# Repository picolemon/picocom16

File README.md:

# Picocom16
A DIY breadboard computer based on four RP2350 micro controllers that can be built without any soldering.

## Features
Easy build with no soldering.

Fast debugging using VSCode and a usb cable.

Double buffered frame buffer with simple gpu for drawing.

Async DMA bus distributes graphics and sound to each core.

Written in C with a clear and simple api.

## Display

Frame buffer: 320×224, 16 bit color palette, 60 Hz.    

GPU Method: Command dispatch and Tiling.

Blend modes:  4bit alpha composite, Additive blending.

## Memory

System RAM: 512 KB SRAM

VRAM: 512 KB SRAM

FB: 512 KB SRAM

Audio RAM: 512 KB SRAM

## DMA
VDP1 Bus - System to VDP gpu command stream async.

VDP2 Bus - VDP1 to VDP2 tile stream.

APU Bus - System to APU audio commands, audio streams, HID inputs and SD Card IO.

## Storage
Physics format: Format: SD memory card.

File System: Fat32.

## Audio
DSP mixer: play, pause, pan & frequency.

Audio formats: Raw PCM 16, OGG vorbis.

Streaming: Audio stream buffer for seamless audio looping and streaming from System core.

Rate: 11 Khz.

Output: Stereo output via 3mm jack.

Channels: 32 channels ( sfx or ogg in any combination ).

## Cores
APU - Dedicated audio processor. [ [src](sw/apu) ] [ [uf2](firmware/apu.uf2) ]

System - Game processor for game logic, building graphics and audio commands.  [ [demos](sw/demos) ] 

VDP1 - Graphics tile generator.  [ [src](sw/vdp1) ] [ [uf2](firmware/vdp1.uf2) ]

VDP2 - Tile compositor and DVI output.  [ [src](sw/vdp2) ] [ [uf2](firmware/vdp2.uf2) ]

## Examples

gfx_demo [ [src](sw/demos/gfx_demo) ] [ [uf2](firmware/gfx_demo.uf2) ]

input_demo  [ [src](sw/demos/gfx_demo) ] [ [uf2](firmware/gfx_demo.uf2) ]

minerload   [ [demo](https://picocom16.itch.io/minerload) ] [ [uf2](firmware/minerload.uf2) ]

## Components BOM

All components can be source from amazon or other suppliers.

    1 x Breadboard kit - SUNFOUNDER 5PCS Breadboards Kit Include 3PCS 830 Point 2PCS 400 Point Solderless Breadboard Compatible with Arduino Proto Shield Distribution Connecting Blocks 

    1 x Wire kit - 560 Pcs Jumper Wire Kit, 14 Lengths Assorted Preformed Breadboard Jumper Wires, Male to Male Solderless Jumper Cables with Storage Box for Prototyping, LED Strips, and Test Circuits 

    4 x Pre-Soldered Raspberry Pi Pico 2 with Header RP2350 Microcontroller Board Mini Board Kit Based on RP2350 Chip,Dual-core & Dual-architecture,Support C/C++/Python 

    1 x PCM5102 DAC Decoder Module I2S Interface GY-PCM5102 PHAT Format Player Board Digital-to-Analog Converter Voice Module for Arduino, Raspberry Pi with 3.5mm Jack Audio Cable, Dupont Cable 

    1 x AZDelivery Micro SD SPI Storage Board TF Memory Card Adapter Shield Module 5V compatible with Arduino Including E-Book! (Pack of 3) 

    1 x Adafruit DVI Breakout Board - For HDMI Source Devices 

    1 x 18pcs USB to DIP Breakout Adapter Converter Mini 5p USB/2.54 mm 4p/USB 2.0 4p/USB 3.0 Flat/Micro USB Type B/USB Type-B Square PCB Power Breakout Board Module

## Build guide
This is what the fully assembled breadboard looks like:

See [docs/guides/picocom16-breadboard/Build-guide.md](docs/guides/picocom16-breadboard/Build-guide.md)

## System dependencies

VSCode: https://code.visualstudio.com/

Pico sdk: https://marketplace.visualstudio.com/items?itemName=raspberry-pi.raspberry-pi-pico

Asset tooling python deps
```
pip install bdfparser
```

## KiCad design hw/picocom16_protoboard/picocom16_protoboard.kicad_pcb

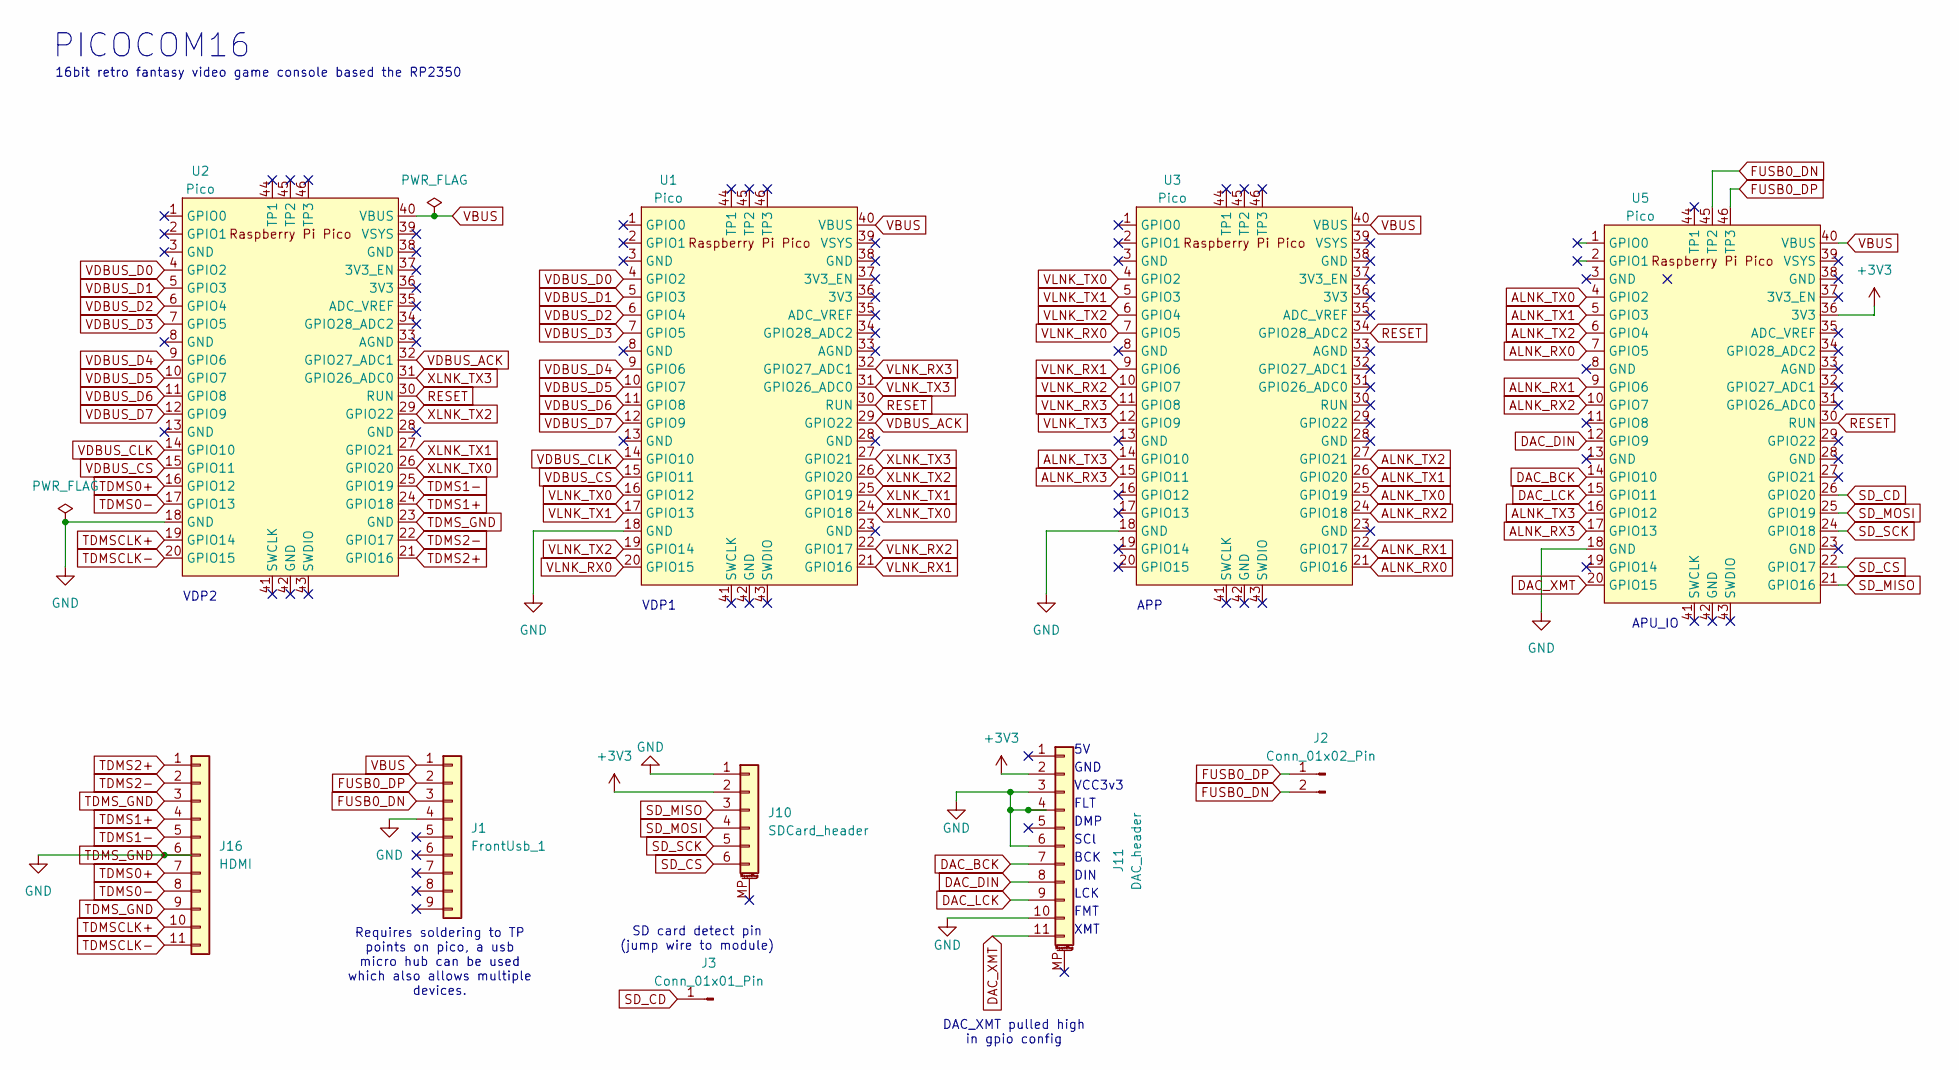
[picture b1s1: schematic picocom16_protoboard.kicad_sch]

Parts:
J1: FrontUsb_1; PinHeader_1x09_P2.54mm_Vertical
J2: Conn_01x02_Pin; PinHeader_1x02_P2.54mm_Vertical
J3: Conn_01x01_Pin; PinHeader_1x01_P2.54mm_Vertical
J10: SDCard_header; PinHeader_1x06_P2.54mm_Vertical
J11: DAC_header; PinHeader_1x11_P2.54mm_Vertical
J16: HDMI; PinHeader_1x11_P2.54mm_Vertical
U1, U2, U3, U5: Pico; RPi_Pico_SMD_TH

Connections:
+3V3: J10.2, J11.2, U5.36 (3V3)
ALNK_RX0: U3.21 (GPIO16), U5.7 (GPIO5)
ALNK_RX1: U3.22 (GPIO17), U5.9 (GPIO6)
ALNK_RX2: U3.24 (GPIO18), U5.10 (GPIO7)
ALNK_RX3: U3.15 (GPIO11), U5.17 (GPIO13)
ALNK_TX0: U3.25 (GPIO19), U5.4 (GPIO2)
ALNK_TX1: U3.26 (GPIO20), U5.5 (GPIO3)
ALNK_TX2: U3.27 (GPIO21), U5.6 (GPIO4)
ALNK_TX3: U3.14 (GPIO10), U5.16 (GPIO12)
DAC_BCK: J11.7, U5.14 (GPIO10)
DAC_DIN: J11.8, U5.12 (GPIO9)
DAC_LCK: J11.9, U5.15 (GPIO11)
DAC_XMT: J11.11, U5.20 (GPIO15)
FUSB0_DN: J1.3, J2.2, U5.45 (TP2)
FUSB0_DP: J1.2, J2.1, U5.46 (TP3)
RESET: U1.30 (RUN), U2.30 (RUN), U3.34 (GPIO28_ADC2), U5.30 (RUN)
SD_CD: J3.1, U5.26 (GPIO20)
SD_CS: J10.6, U5.22 (GPIO17)
SD_MISO: J10.3, U5.21 (GPIO16)
SD_MOSI: J10.4, U5.25 (GPIO19)
SD_SCK: J10.5, U5.24 (GPIO18)
TDMS0+: J16.7, U2.16 (GPIO12)
TDMS0-: J16.8, U2.17 (GPIO13)
TDMS1+: J16.4, U2.24 (GPIO18)
TDMS1-: J16.5, U2.25 (GPIO19)
TDMS2+: J16.1, U2.21 (GPIO16)
TDMS2-: J16.2, U2.22 (GPIO17)
TDMSCLK+: J16.10, U2.19 (GPIO14)
TDMSCLK-: J16.11, U2.20 (GPIO15)
TDMS_GND: J1.4, J10.1, J11.3, J11.4, J11.6, J11.10, J16.3, J16.6, J16.9, U1.18 (GND), U2.18 (GND), U2.23 (GND), U3.18 (GND), U5.18 (GND)
VBUS: J1.1, U1.40 (VBUS), U2.40 (VBUS), U3.40 (VBUS), U5.40 (VBUS)
VDBUS_ACK: U1.29 (GPIO22), U2.32 (GPIO27_ADC1)
VDBUS_CLK: U1.14 (GPIO10), U2.14 (GPIO10)
VDBUS_CS: U1.15 (GPIO11), U2.15 (GPIO11)
VDBUS_D0: U1.4 (GPIO2), U2.4 (GPIO2)
VDBUS_D1: U1.5 (GPIO3), U2.5 (GPIO3)
VDBUS_D2: U1.6 (GPIO4), U2.6 (GPIO4)
VDBUS_D3: U1.7 (GPIO5), U2.7 (GPIO5)
VDBUS_D4: U1.9 (GPIO6), U2.9 (GPIO6)
VDBUS_D5: U1.10 (GPIO7), U2.10 (GPIO7)
VDBUS_D6: U1.11 (GPIO8), U2.11 (GPIO8)
VDBUS_D7: U1.12 (GPIO9), U2.12 (GPIO9)
VLNK_RX0: U1.20 (GPIO15), U3.7 (GPIO5)
VLNK_RX1: U1.21 (GPIO16), U3.9 (GPIO6)
VLNK_RX2: U1.22 (GPIO17), U3.10 (GPIO7)
VLNK_RX3: U1.32 (GPIO27_ADC1), U3.11 (GPIO8)
VLNK_TX0: U1.16 (GPIO12), U3.4 (GPIO2)
VLNK_TX1: U1.17 (GPIO13), U3.5 (GPIO3)
VLNK_TX2: U1.19 (GPIO14), U3.6 (GPIO4)
VLNK_TX3: U1.31 (GPIO26_ADC0), U3.12 (GPIO9)
XLNK_TX0: U1.24 (GPIO18), U2.26 (GPIO20)
XLNK_TX1: U1.25 (GPIO19), U2.27 (GPIO21)
XLNK_TX2: U1.26 (GPIO20), U2.29 (GPIO22)
XLNK_TX3: U1.27 (GPIO21), U2.31 (GPIO26_ADC0)

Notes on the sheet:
APP
VDP1
VCC3v3
FMT
DMP
DIN
SD card detect pin (jump wire to module)
16bit retro fantasy video game console based the RP2350
XMT
VDP2
FLT
GND
SCl
DAC_XMT pulled high in gpio config
Requires soldering to TP points on pico, a usb micro hub can be used which also allows multiple devices.
PICOCOM16
APU_IO
LCK
BCK

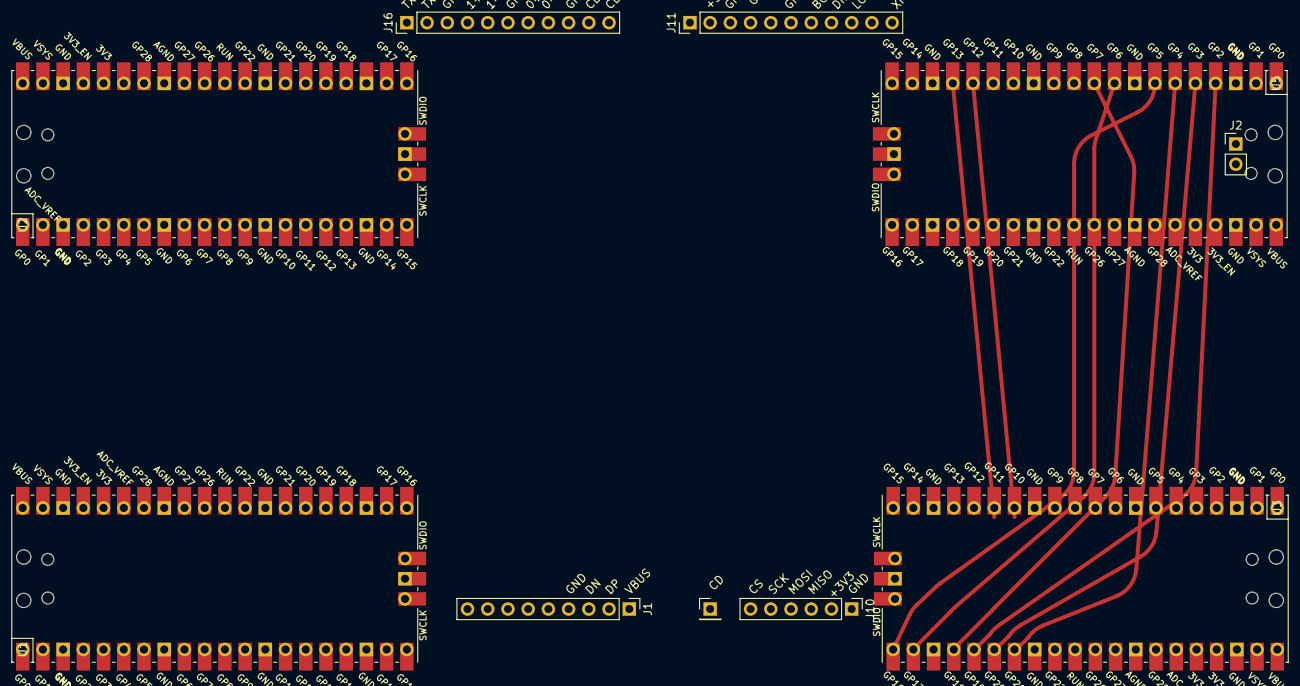
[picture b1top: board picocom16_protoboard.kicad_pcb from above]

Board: 18 copper layers, 10 parts (0 on the bottom side), 54 nets.

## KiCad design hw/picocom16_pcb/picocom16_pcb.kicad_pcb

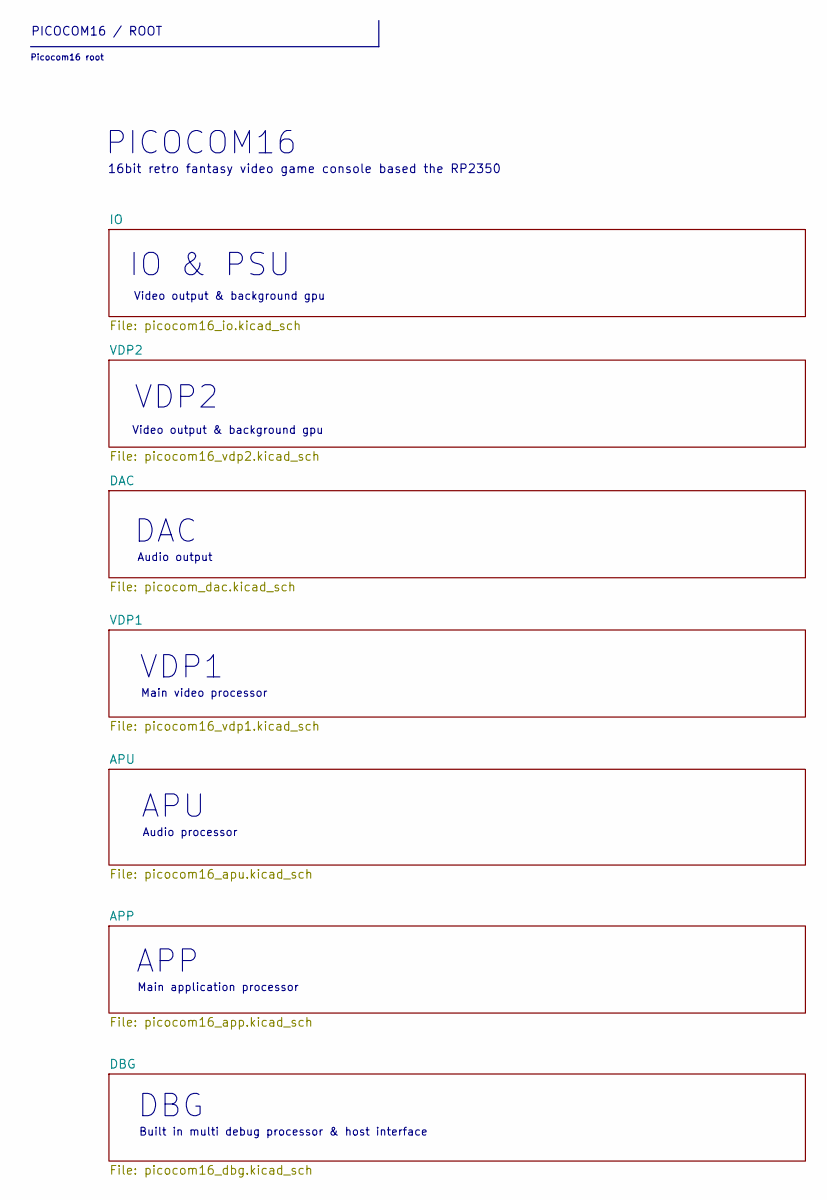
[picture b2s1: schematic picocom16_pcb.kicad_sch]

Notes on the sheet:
VDP2
Main application processor
Audio output
Built in multi debug processor & host interface
PICOCOM16 / ROOT
Video output & background gpu
VDP1
IO & PSU
16bit retro fantasy video game console based the RP2350
APP
Picocom16 root
Main video processor
DBG
APU
PICOCOM16
DAC
Audio processor

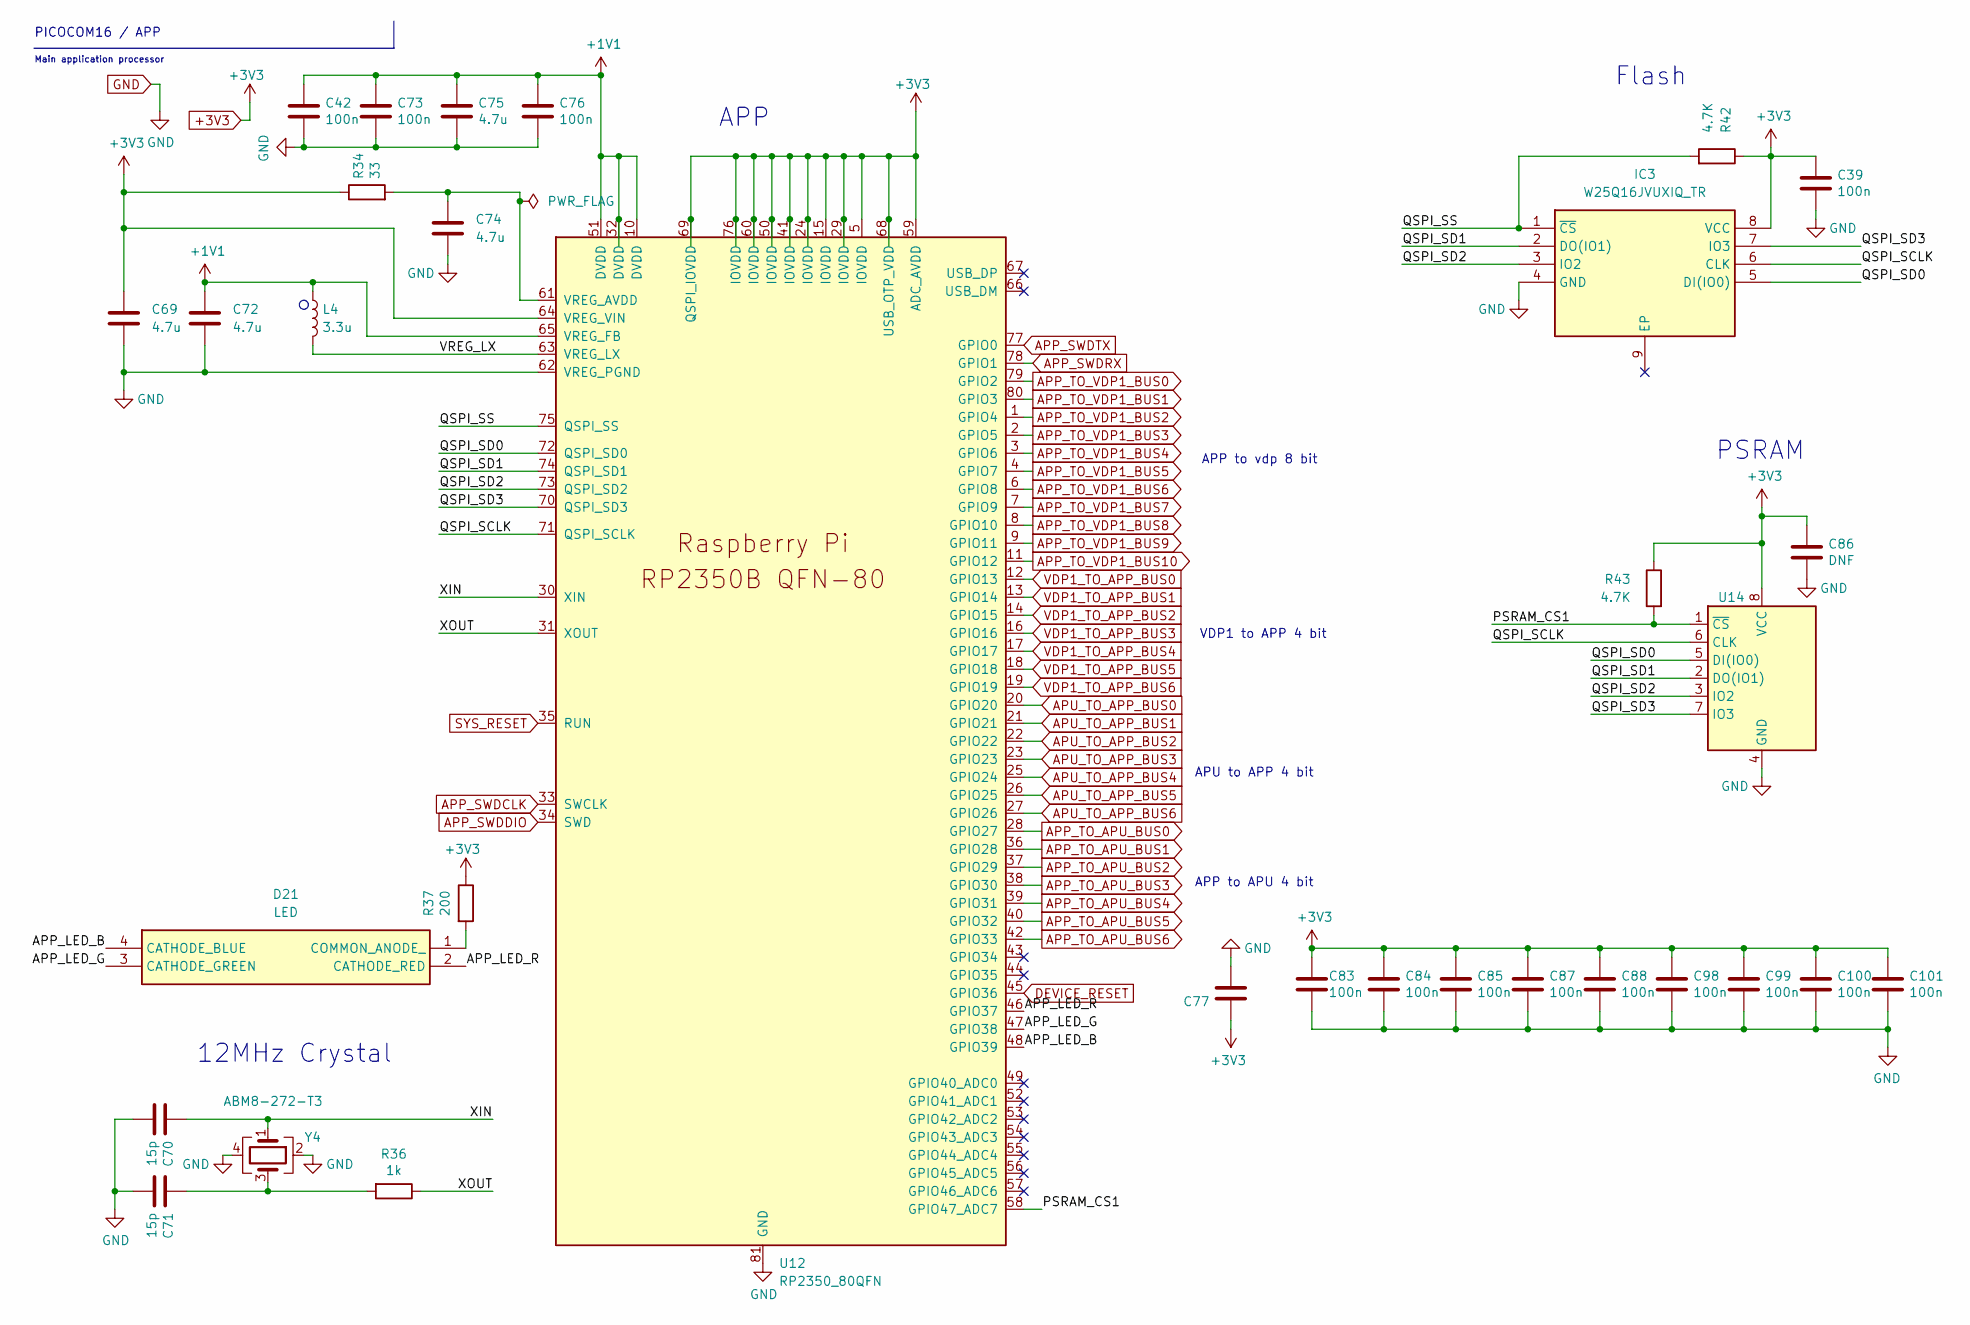
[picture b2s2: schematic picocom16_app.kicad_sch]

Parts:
C39, C42, C73, C76, C83, C84, C85, C87, C88, C98, C99, C100, C101: 100n; C_0402_1005Metric
C69, C72, C74, C75: 4.7u; C_0402_1005Metric
C70, C71: 15p; C_0402_1005Metric
C77: 10u; C_0805_2012Metric
C86: DNF; C_0402_1005Metric
D21: LRTBR48G-P9Q7-1+R7S5-26+NP-68; LRTBR48GP9Q71R7S526NP68; Mouser Part Number 720-LRTBR48GP9A3521
IC3: W25Q16JVUXIQ_TR; SON50P300X200X60-9N; Mouser Part Number 454-W25Q16JVUXIQTR
L4: 3.3u; L_0805_2012Metric
R34: 33; R_0402_1005Metric
R36: 1k; R_0402_1005Metric
R37: 200; R_0402_1005Metric
R42, R43: 4.7K; R_0402_1005Metric
U12: RP2350_80QFN; RP2350-QFN-80-1EP_10x10_P0.4mm_EP3.4x3.4mm_ThermalVias
U14: SOIC-8_5.23x5.23mm_P1.27mm
Y4: ABM8-272-T3; ABM8272T3

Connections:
+1V1: C42.1, C72.1, C73.1, C75.1, C76.1, L4.1, U12.10 (DVDD), U12.32 (DVDD), U12.51 (DVDD), U12.65 (VREG_FB); also elsewhere on the board
+3V3: C39.1, C69.1, C77.1, C83.1, C84.1, C85.1, C86.1, C87.1, C88.1, C98.1, C99.1, C100.1, C101.1, IC3.8 (VCC), R34.1, R37.1, R42.1, R43.1, U12.5 (IOVDD), U12.15 (IOVDD), U12.24 (IOVDD), U12.29 (IOVDD), U12.41 (IOVDD), U12.50 (IOVDD), U12.59 (ADC_AVDD), U12.60 (IOVDD), U12.64 (VREG_VIN), U12.68 (USB_OTP_VDD), U12.69 (QSPI_IOVDD), U12.76 (IOVDD), U14.8 (VCC); also elsewhere on the board
/APP/APP_LED_B: D21.4 (CATHODE_BLUE), U12.48 (GPIO39)
/APP/APP_LED_G: D21.3 (CATHODE_GREEN), U12.47 (GPIO38)
/APP/APP_LED_R: D21.2 (CATHODE_RED), U12.46 (GPIO37)
/APP/PSRAM_CS1: R43.2, U12.58 (GPIO47_ADC7), U14.1 (~CS)
/APP/QSPI_SCLK: IC3.6 (CLK), U12.71 (QSPI_SCLK), U14.6 (CLK)
/APP/QSPI_SD0: IC3.5 (DI(IO0)), U12.72 (QSPI_SD0), U14.5 (DI(IO0))
/APP/QSPI_SD1: IC3.2 (DO(IO1)), U12.74 (QSPI_SD1), U14.2 (DO(IO1))
/APP/QSPI_SD2: IC3.3 (IO2), U12.73 (QSPI_SD2), U14.3 (IO2)
/APP/QSPI_SD3: IC3.7 (IO3), U12.70 (QSPI_SD3), U14.7 (IO3)
/APP/QSPI_SS: IC3.1 (~CS), R42.2, U12.75 (QSPI_SS)
/APP/VREG_LX: L4.2, U12.63 (VREG_LX)
/APP/XIN: C70.1, U12.30 (XIN), Y4.1
/APP/XOUT: R36.1, U12.31 (XOUT)
APP_SWDCLK: U12.33 (SWCLK); also elsewhere on the board
APP_SWDDIO: U12.34 (SWD); also elsewhere on the board
APP_SWDRX: U12.78 (GPIO1); also elsewhere on the board
APP_SWDTX: U12.77 (GPIO0); also elsewhere on the board
APP_TO_APU_BUS0: U12.28 (GPIO27); also elsewhere on the board
APP_TO_APU_BUS1: U12.36 (GPIO28); also elsewhere on the board
APP_TO_APU_BUS2: U12.37 (GPIO29); also elsewhere on the board
APP_TO_APU_BUS3: U12.38 (GPIO30); also elsewhere on the board
APP_TO_APU_BUS4: U12.39 (GPIO31); also elsewhere on the board
APP_TO_APU_BUS5: U12.40 (GPIO32); also elsewhere on the board
APP_TO_APU_BUS6: U12.42 (GPIO33); also elsewhere on the board
APP_TO_VDP1_BUS0: U12.79 (GPIO2); also elsewhere on the board
APP_TO_VDP1_BUS1: U12.80 (GPIO3); also elsewhere on the board
APP_TO_VDP1_BUS2: U12.1 (GPIO4); also elsewhere on the board
APP_TO_VDP1_BUS3: U12.2 (GPIO5); also elsewhere on the board
APP_TO_VDP1_BUS4: U12.3 (GPIO6); also elsewhere on the board
APP_TO_VDP1_BUS5: U12.4 (GPIO7); also elsewhere on the board
APP_TO_VDP1_BUS6: U12.6 (GPIO8); also elsewhere on the board
APP_TO_VDP1_BUS7: U12.7 (GPIO9); also elsewhere on the board
APP_TO_VDP1_BUS8: U12.8 (GPIO10); also elsewhere on the board
APP_TO_VDP1_BUS9: U12.9 (GPIO11); also elsewhere on the board
APP_TO_VDP1_BUS10: U12.11 (GPIO12); also elsewhere on the board
APU_TO_APP_BUS0: U12.20 (GPIO20); also elsewhere on the board
APU_TO_APP_BUS1: U12.21 (GPIO21); also elsewhere on the board
APU_TO_APP_BUS2: U12.22 (GPIO22); also elsewhere on the board
APU_TO_APP_BUS3: U12.23 (GPIO23); also elsewhere on the board
APU_TO_APP_BUS4: U12.25 (GPIO24); also elsewhere on the board
APU_TO_APP_BUS5: U12.26 (GPIO25); also elsewhere on the board
APU_TO_APP_BUS6: U12.27 (GPIO26); also elsewhere on the board
DEVICE_RESET: U12.45 (GPIO36); also elsewhere on the board
GND: C39.2, C42.2, C69.2, C70.2, C71.2, C72.2, C73.2, C74.2, C75.2, C76.2, C77.2, C83.2, C84.2, C85.2, C86.2, C87.2, C88.2, C98.2, C99.2, C100.2, C101.2, IC3.4 (GND), U12.62 (VREG_PGND), U12.81 (GND), U14.4 (GND), Y4.2, Y4.4; also elsewhere on the board
unnamed: C71.1, R36.2, Y4.3
unnamed: D21.1 (COMMON_ANODE_), R37.2
unnamed: C74.1, R34.2, U12.61 (VREG_AVDD)
SYS_RESET: U12.35 (RUN); also elsewhere on the board
VDP1_TO_APP_BUS0: U12.12 (GPIO13); also elsewhere on the board
VDP1_TO_APP_BUS1: U12.13 (GPIO14); also elsewhere on the board
VDP1_TO_APP_BUS2: U12.14 (GPIO15); also elsewhere on the board
VDP1_TO_APP_BUS3: U12.16 (GPIO16); also elsewhere on the board
VDP1_TO_APP_BUS4: U12.17 (GPIO17); also elsewhere on the board
VDP1_TO_APP_BUS5: U12.18 (GPIO18); also elsewhere on the board
VDP1_TO_APP_BUS6: U12.19 (GPIO19); also elsewhere on the board

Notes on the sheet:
PSRAM
APP to APU 4 bit
APP to vdp 8 bit
APP
APU to APP 4 bit
12MHz Crystal
PICOCOM16 / APP
Main application processor
VDP1 to APP 4 bit
Flash

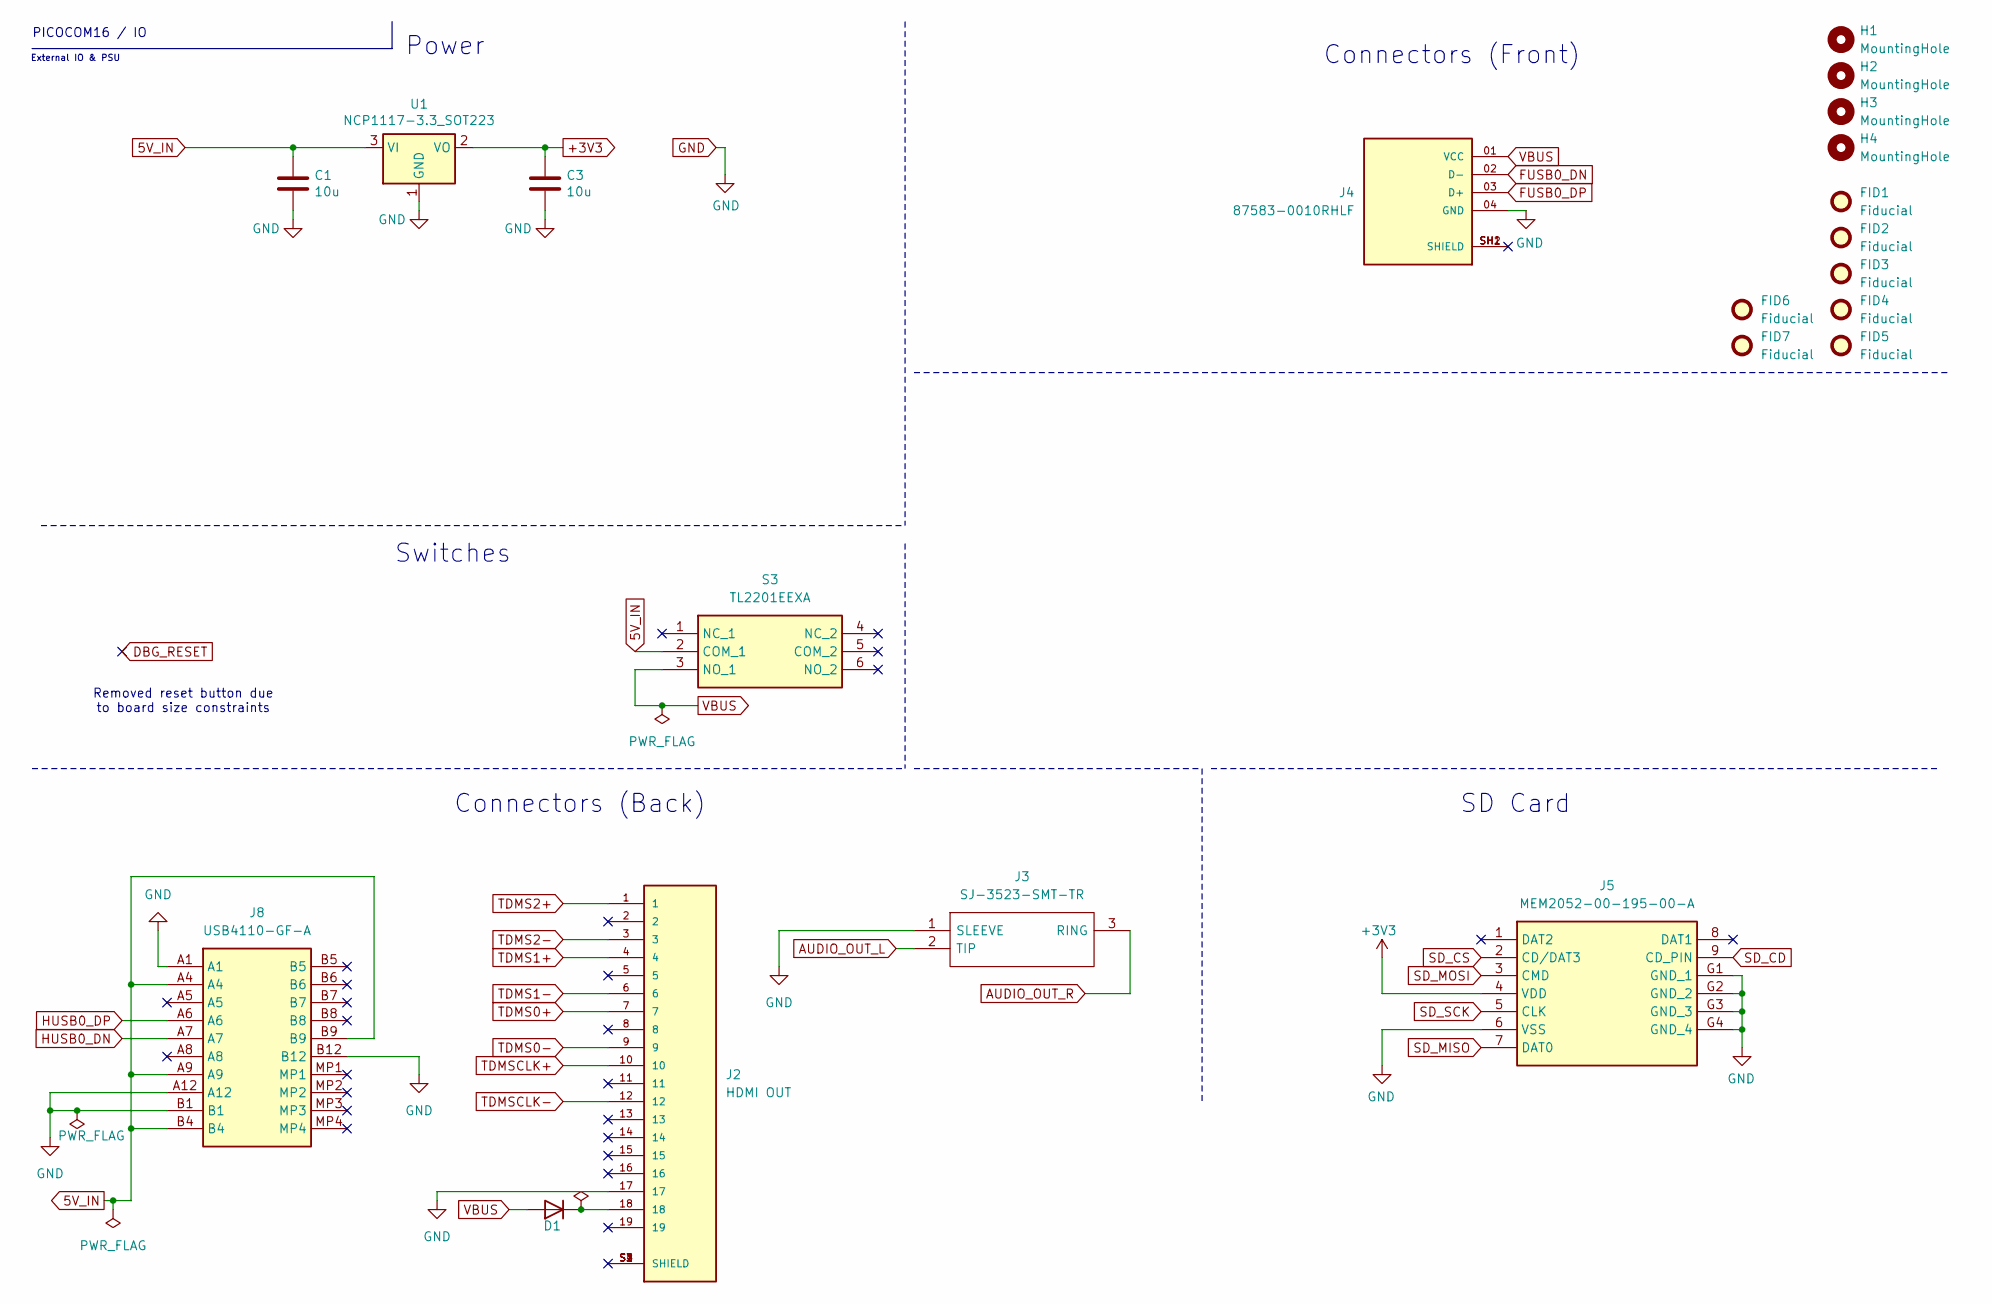
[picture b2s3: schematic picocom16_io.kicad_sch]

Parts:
C1, C3: 10u; C_0805_2012Metric
D1: D; SODFL1608X70N
FID1, FID2, FID3, FID4, FID6, FID7: Fiducial; Fiducial_1mm_Mask2mm
FID5: Fiducial; Fiducial_0.5mm_Mask1.5mm
H1, H2, H3, H4: MountingHole; MountingHole_2.7mm_M2.5
J2: HDMI OUT; STEWART_SS-53000-001; PARTREV A0
J3: SJ-3523-SMT-TR; SJ3523SMTTR; Mouser Part Number 490-SJ-3523-SMT-TR
J4: 87583-0010RHLF; AMPHENOL_87583-0010RHLF; PARTREV AD
J5: MEM2052-00-195-00-A; MEM20520019500A; Mouser Part Number 640-MEM20520019500A
J8: USB4110-GF-A; USB4110GFA; Mouser Part Number 640-USB4110-GF-A
S3: TL2201EEXA; Mouser Part Number 612-TL2201EEXA
U1: NCP1117-3.3_SOT223; SOT-223-3_TabPin2

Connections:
5V_IN: C1.1, J8.A4, J8.A9, J8.B4, J8.B9, S3.2 (COM_1), U1.3 (VI)
+3V3: C3.1, J5.4 (VDD), U1.2 (VO); also elsewhere on the board
AUDIO_OUT_L: J3.2 (TIP); also elsewhere on the board
AUDIO_OUT_R: J3.3 (RING); also elsewhere on the board
FUSB0_DN: J4.02 (D-); also elsewhere on the board
FUSB0_DP: J4.03 (D+); also elsewhere on the board
GND: C1.2, C3.2, J2.17, J3.1 (SLEEVE), J4.04 (GND), J5.6 (VSS), J5.G1 (GND_1), J5.G2 (GND_2), J5.G3 (GND_3), J5.G4 (GND_4), J8.A1, J8.A12, J8.B1, J8.B12, U1.1 (GND); also elsewhere on the board
HUSB0_DN: J8.A7; also elsewhere on the board
HUSB0_DP: J8.A6; also elsewhere on the board
unnamed: D1.1 (K), J2.18
SD_CD: J5.9 (CD_PIN); also elsewhere on the board
SD_CS: J5.2 (CD/DAT3); also elsewhere on the board
SD_MISO: J5.7 (DAT0); also elsewhere on the board
SD_MOSI: J5.3 (CMD); also elsewhere on the board
SD_SCK: J5.5 (CLK); also elsewhere on the board
TDMS0+: J2.7; also elsewhere on the board
TDMS0-: J2.9; also elsewhere on the board
TDMS1+: J2.4; also elsewhere on the board
TDMS1-: J2.6; also elsewhere on the board
TDMS2+: J2.1; also elsewhere on the board
TDMS2-: J2.3; also elsewhere on the board
TDMSCLK+: J2.10; also elsewhere on the board
TDMSCLK-: J2.12; also elsewhere on the board
VBUS: D1.2 (A), J4.01 (VCC), S3.3 (NO_1)

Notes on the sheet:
External IO & PSU
PICOCOM16 / IO
Power
Connectors (Front)
Switches
Removed reset button due to board size constraints
Connectors (Back)
SD Card

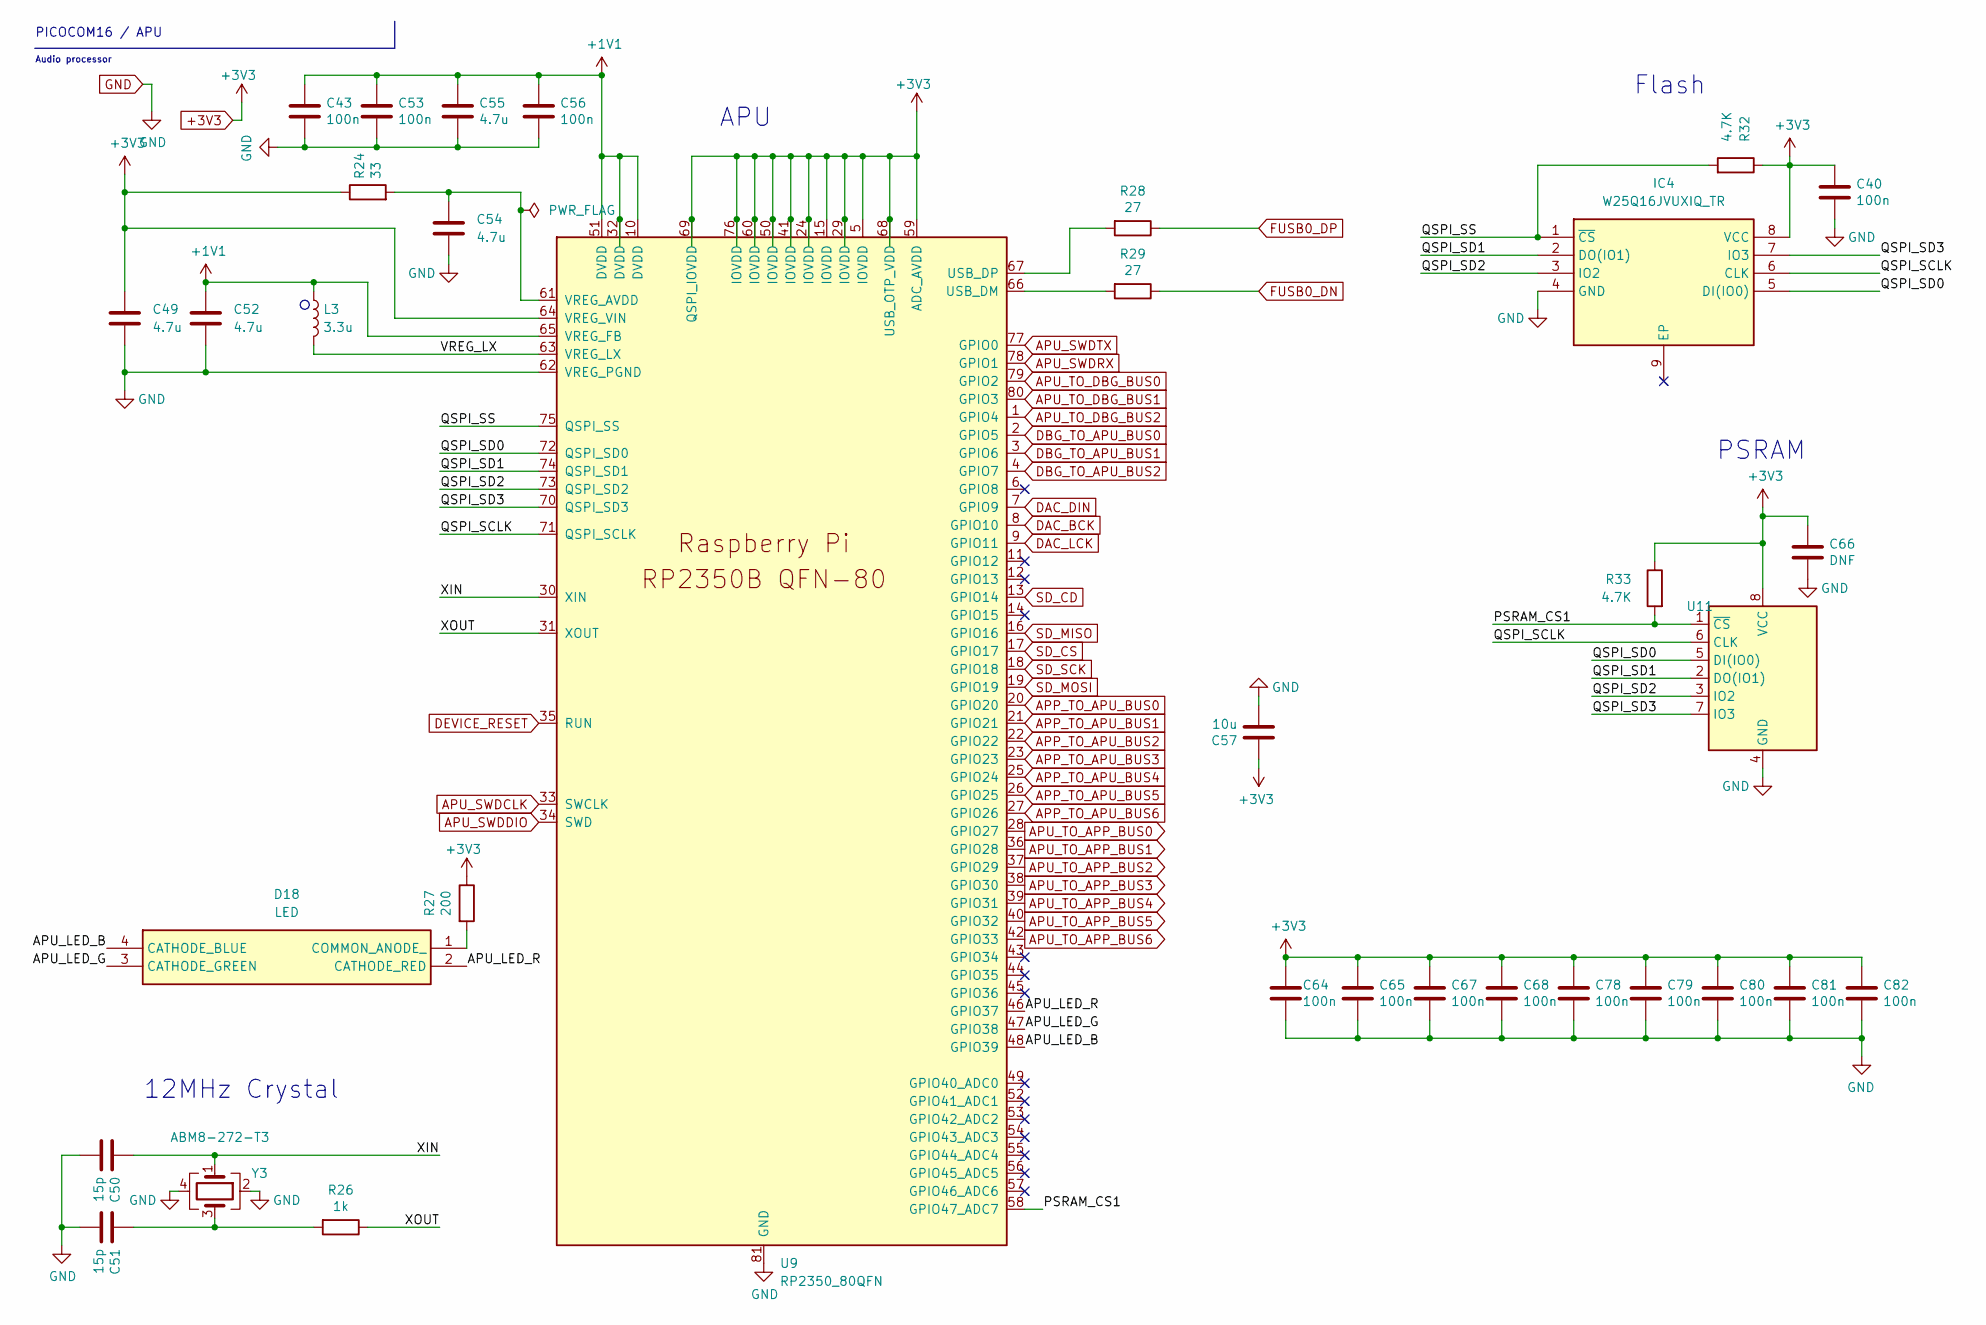
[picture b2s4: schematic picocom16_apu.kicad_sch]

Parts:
C40, C43, C53, C56, C64, C65, C67, C68, C78, C79, C80, C81, C82: 100n; C_0402_1005Metric
C49, C52, C54, C55: 4.7u; C_0402_1005Metric
C50, C51: 15p; C_0402_1005Metric
C57: 10u; C_0805_2012Metric
C66: DNF; C_0402_1005Metric
D18: LRTBR48G-P9Q7-1+R7S5-26+NP-68; LRTBR48GP9Q71R7S526NP68; Mouser Part Number 720-LRTBR48GP9A3521
IC4: W25Q16JVUXIQ_TR; SON50P300X200X60-9N; Mouser Part Number 454-W25Q16JVUXIQTR
L3: 3.3u; L_0805_2012Metric
R24: 33; R_0402_1005Metric
R26: 1k; R_0402_1005Metric
R27: 200; R_0402_1005Metric
R28, R29: 27; R_0402_1005Metric
R32, R33: 4.7K; R_0402_1005Metric
U9: RP2350_80QFN; RP2350-QFN-80-1EP_10x10_P0.4mm_EP3.4x3.4mm_ThermalVias
U11: SOIC-8_5.23x5.23mm_P1.27mm
Y3: ABM8-272-T3; ABM8272T3

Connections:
+1V1: C43.1, C52.1, C53.1, C55.1, C56.1, L3.1, U9.10 (DVDD), U9.32 (DVDD), U9.51 (DVDD), U9.65 (VREG_FB); also elsewhere on the board
+3V3: C40.1, C49.1, C57.1, C64.1, C65.1, C66.1, C67.1, C68.1, C78.1, C79.1, C80.1, C81.1, C82.1, IC4.8 (VCC), R24.1, R27.1, R32.1, R33.1, U9.5 (IOVDD), U9.15 (IOVDD), U9.24 (IOVDD), U9.29 (IOVDD), U9.41 (IOVDD), U9.50 (IOVDD), U9.59 (ADC_AVDD), U9.60 (IOVDD), U9.64 (VREG_VIN), U9.68 (USB_OTP_VDD), U9.69 (QSPI_IOVDD), U9.76 (IOVDD), U11.8 (VCC); also elsewhere on the board
/APU/APU_LED_B: D18.4 (CATHODE_BLUE), U9.48 (GPIO39)
/APU/APU_LED_G: D18.3 (CATHODE_GREEN), U9.47 (GPIO38)
/APU/APU_LED_R: D18.2 (CATHODE_RED), U9.46 (GPIO37)
/APU/PSRAM_CS1: R33.2, U9.58 (GPIO47_ADC7), U11.1 (~CS)
/APU/QSPI_SCLK: IC4.6 (CLK), U9.71 (QSPI_SCLK), U11.6 (CLK)
/APU/QSPI_SD0: IC4.5 (DI(IO0)), U9.72 (QSPI_SD0), U11.5 (DI(IO0))
/APU/QSPI_SD1: IC4.2 (DO(IO1)), U9.74 (QSPI_SD1), U11.2 (DO(IO1))
/APU/QSPI_SD2: IC4.3 (IO2), U9.73 (QSPI_SD2), U11.3 (IO2)
/APU/QSPI_SD3: IC4.7 (IO3), U9.70 (QSPI_SD3), U11.7 (IO3)
/APU/QSPI_SS: IC4.1 (~CS), R32.2, U9.75 (QSPI_SS)
/APU/VREG_LX: L3.2, U9.63 (VREG_LX)
/APU/XIN: C50.1, U9.30 (XIN), Y3.1
/APU/XOUT: R26.1, U9.31 (XOUT)
APP_TO_APU_BUS0: U9.20 (GPIO20); also elsewhere on the board
APP_TO_APU_BUS1: U9.21 (GPIO21); also elsewhere on the board
APP_TO_APU_BUS2: U9.22 (GPIO22); also elsewhere on the board
APP_TO_APU_BUS3: U9.23 (GPIO23); also elsewhere on the board
APP_TO_APU_BUS4: U9.25 (GPIO24); also elsewhere on the board
APP_TO_APU_BUS5: U9.26 (GPIO25); also elsewhere on the board
APP_TO_APU_BUS6: U9.27 (GPIO26); also elsewhere on the board
APU_SWDCLK: U9.33 (SWCLK); also elsewhere on the board
APU_SWDDIO: U9.34 (SWD); also elsewhere on the board
APU_SWDRX: U9.78 (GPIO1); also elsewhere on the board
APU_SWDTX: U9.77 (GPIO0); also elsewhere on the board
APU_TO_APP_BUS0: U9.28 (GPIO27); also elsewhere on the board
APU_TO_APP_BUS1: U9.36 (GPIO28); also elsewhere on the board
APU_TO_APP_BUS2: U9.37 (GPIO29); also elsewhere on the board
APU_TO_APP_BUS3: U9.38 (GPIO30); also elsewhere on the board
APU_TO_APP_BUS4: U9.39 (GPIO31); also elsewhere on the board
APU_TO_APP_BUS5: U9.40 (GPIO32); also elsewhere on the board
APU_TO_APP_BUS6: U9.42 (GPIO33); also elsewhere on the board
APU_TO_DBG_BUS0: U9.79 (GPIO2); also elsewhere on the board
APU_TO_DBG_BUS1: U9.80 (GPIO3); also elsewhere on the board
APU_TO_DBG_BUS2: U9.1 (GPIO4); also elsewhere on the board
DAC_BCK: U9.8 (GPIO10); also elsewhere on the board
DAC_DIN: U9.7 (GPIO9); also elsewhere on the board
DAC_LCK: U9.9 (GPIO11); also elsewhere on the board
DBG_TO_APU_BUS0: U9.2 (GPIO5); also elsewhere on the board
DBG_TO_APU_BUS1: U9.3 (GPIO6); also elsewhere on the board
DBG_TO_APU_BUS2: U9.4 (GPIO7); also elsewhere on the board
DEVICE_RESET: U9.35 (RUN); also elsewhere on the board
ESP_SPI_MISO: U9.44 (GPIO35)
ESP_SPI_MOSI: U9.43 (GPIO34)
FUSB0_DN: R29.1; also elsewhere on the board
FUSB0_DP: R28.1; also elsewhere on the board
GND: C40.2, C43.2, C49.2, C50.2, C51.2, C52.2, C53.2, C54.2, C55.2, C56.2, C57.2, C64.2, C65.2, C66.2, C67.2, C68.2, C78.2, C79.2, C80.2, C81.2, C82.2, IC4.4 (GND), U9.62 (VREG_PGND), U9.81 (GND), U11.4 (GND), Y3.2, Y3.4; also elsewhere on the board
unnamed: C51.1, R26.2, Y3.3
unnamed: D18.1 (COMMON_ANODE_), R27.2
unnamed: R29.2, U9.66 (USB_DM)
unnamed: R28.2, U9.67 (USB_DP)
unnamed: C54.1, R24.2, U9.61 (VREG_AVDD)
SD_CD: U9.13 (GPIO14); also elsewhere on the board
SD_CS: U9.17 (GPIO17); also elsewhere on the board
SD_MISO: U9.16 (GPIO16); also elsewhere on the board
SD_MOSI: U9.19 (GPIO19); also elsewhere on the board
SD_SCK: U9.18 (GPIO18); also elsewhere on the board

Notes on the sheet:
PSRAM
Flash
APU
12MHz Crystal
PICOCOM16 / APU
Audio processor
